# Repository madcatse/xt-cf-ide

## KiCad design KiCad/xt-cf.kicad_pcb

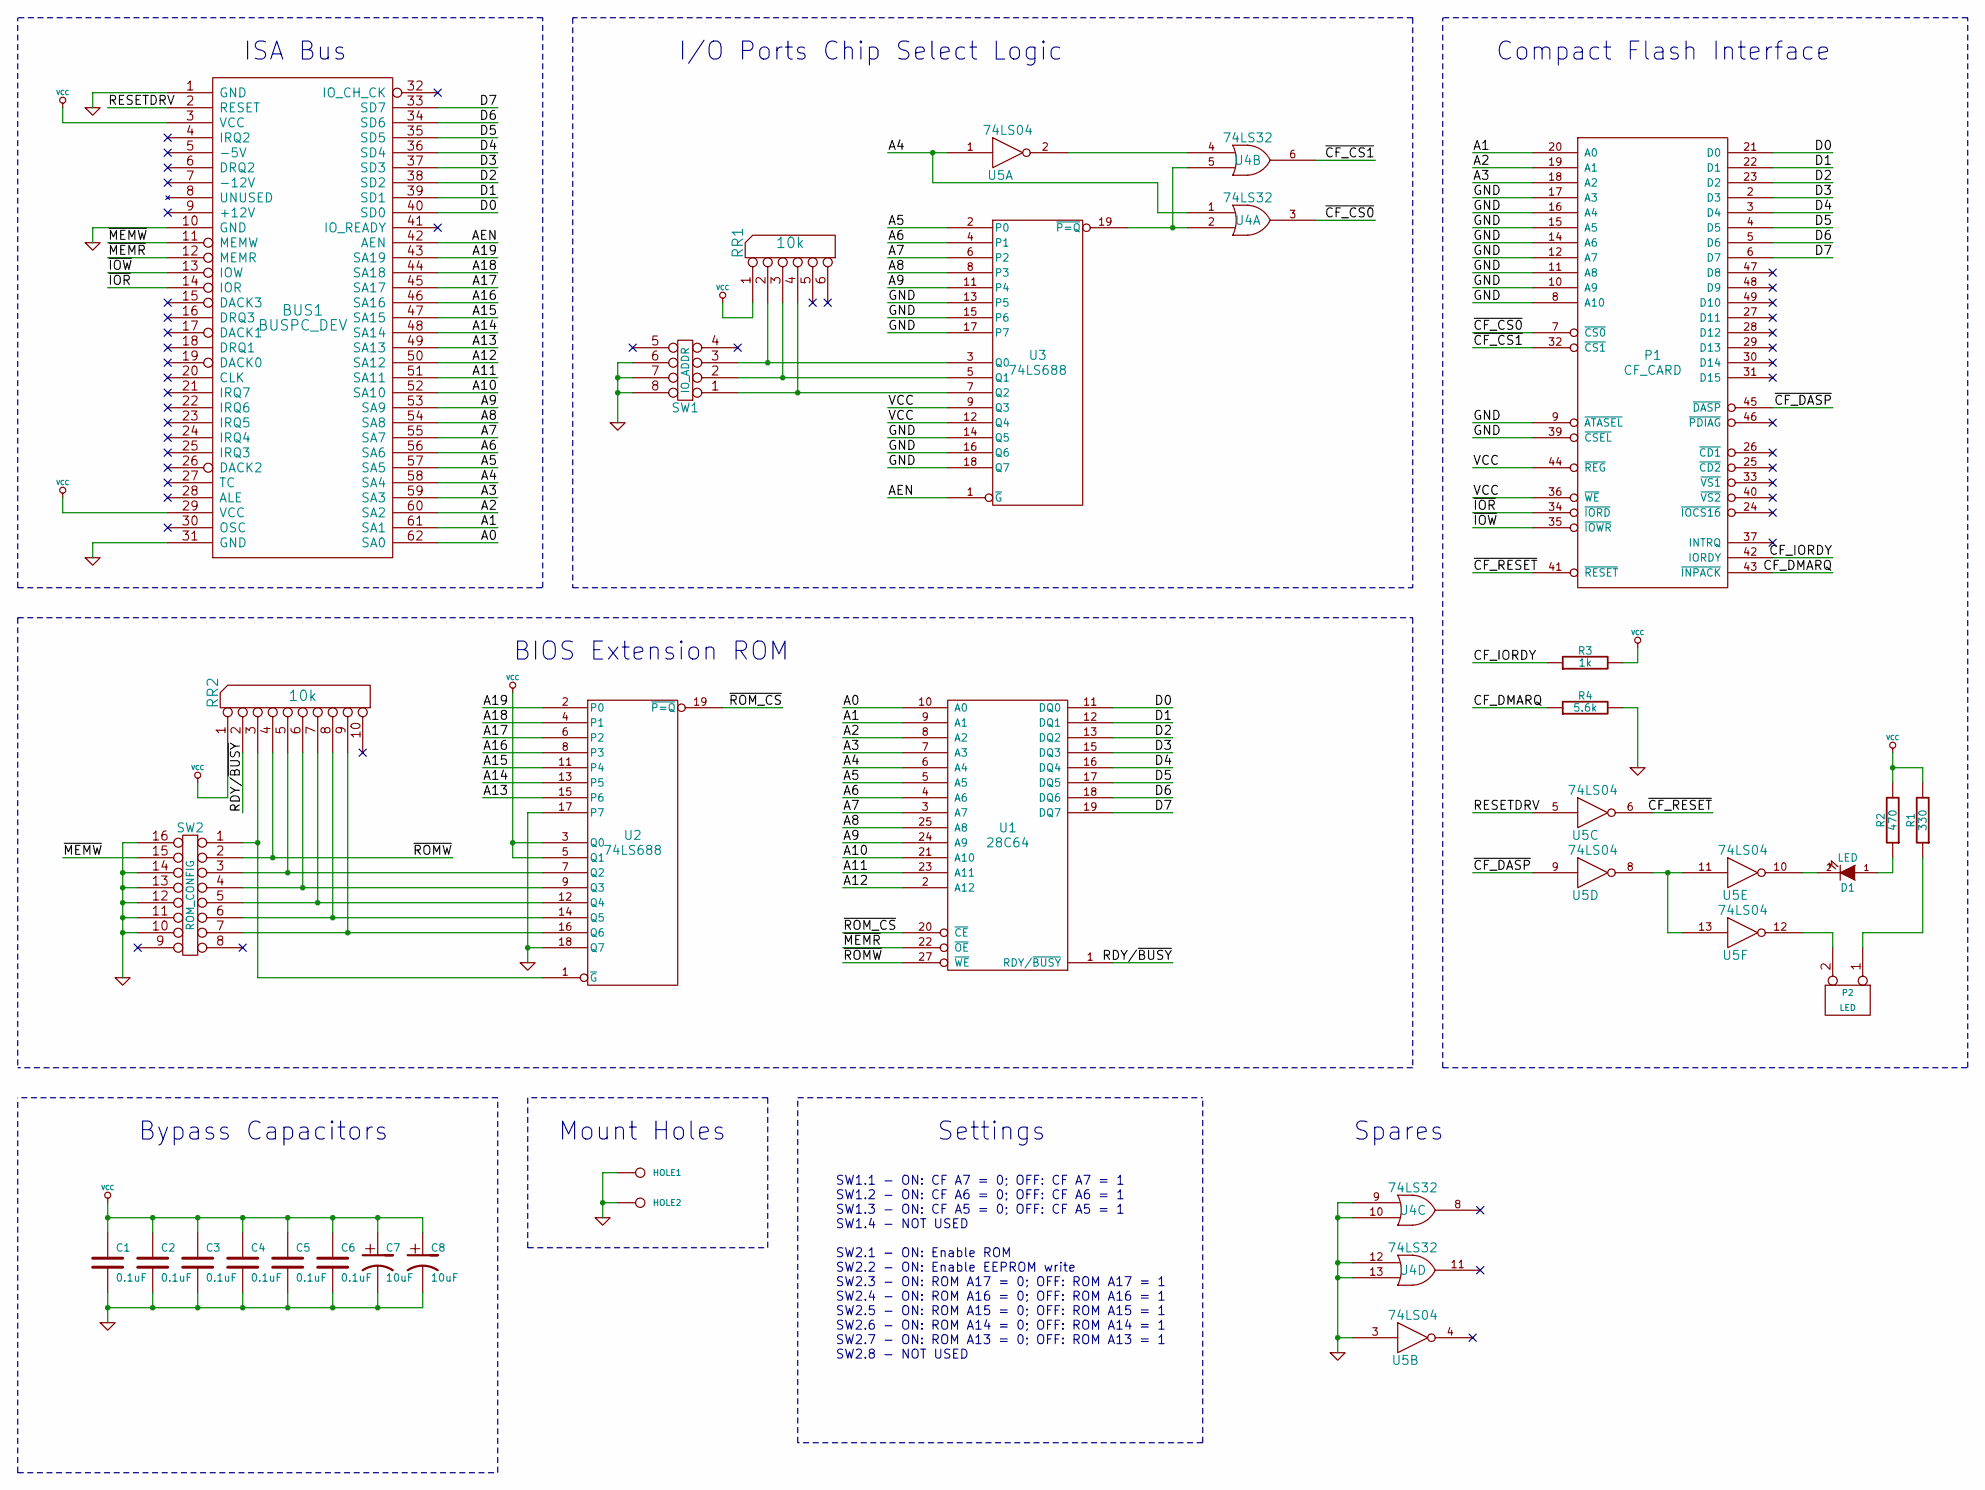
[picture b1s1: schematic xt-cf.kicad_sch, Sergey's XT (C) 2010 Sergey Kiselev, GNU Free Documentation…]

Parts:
BUS1: BUSPC_DEV; Conn_Bus_ISA8
C1, C2, C3, C4, C5, C6: 0.1uF; C_Disc_D7.0mm_W2.5mm_P5.00mm
C7, C8: 10uF; CP_Radial_D8.0mm_P5.00mm
D1: LED; LED_D3.0mm
HOLE1, HOLE2: CONN_1; HOLE_3MM
P1: CF_CARD; CF_N7E50-Q516XX-40
P2: LED; PIN_ARRAY_2X1
R1: 330; R_Axial_DIN0207_L6.3mm_D2.5mm_P7.62mm_Horizontal
R2: 470; R_Axial_DIN0207_L6.3mm_D2.5mm_P7.62mm_Horizontal
R3: 1k; R_Axial_DIN0207_L6.3mm_D2.5mm_P7.62mm_Horizontal
R4: 5.6k; R_Axial_DIN0207_L6.3mm_D2.5mm_P7.62mm_Horizontal
RR1: 10k; SIL-6
RR2: 10k; SIL-10
SW1: IO_ADDR; DIP8_300
SW2: ROM_CONFIG; DIP16_300
U1: 28C64; DIP-28_W15.24mm
U2, U3: 74LS688; DIP-20_W7.62mm
U4: 74LS32; DIP-14_W7.62mm
U5: 74LS04; DIP-14_W7.62mm

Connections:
/A0: BUS1.62 (SA0), U1.10 (A0)
/A1: BUS1.61 (SA1), P1.20 (A0), U1.9 (A1)
/A2: BUS1.60 (SA2), P1.19 (A1), U1.8 (A2)
/A3: BUS1.59 (SA3), P1.18 (A2), U1.7 (A3)
/A4: BUS1.58 (SA4), U1.6 (A4), U4.1, U5.1
/A5: BUS1.57 (SA5), U1.5 (A5), U3.2 (P0)
/A6: BUS1.56 (SA6), U1.4 (A6), U3.4 (P1)
/A7: BUS1.55 (SA7), U1.3 (A7), U3.6 (P2)
/A8: BUS1.54 (SA8), U1.25 (A8), U3.8 (P3)
/A9: BUS1.53 (SA9), U1.24 (A9), U3.11 (P4)
/A10: BUS1.52 (SA10), U1.21 (A10)
/A11: BUS1.51 (SA11), U1.23 (A11)
/A12: BUS1.50 (SA12), U1.2 (A12)
/A13: BUS1.49 (SA13), U2.15 (P6)
/A14: BUS1.48 (SA14), U2.13 (P5)
/A15: BUS1.47 (SA15), U2.11 (P4)
/A16: BUS1.46 (SA16), U2.8 (P3)
/A17: BUS1.45 (SA17), U2.6 (P2)
/A18: BUS1.44 (SA18), U2.4 (P1)
/A19: BUS1.43 (SA19), U2.2 (P0)
/AEN: BUS1.42 (AEN), U3.1 (~G)
/CF_DMARQ: P1.43 (~INPACK), R4.1
/CF_IORDY: P1.42 (IORDY), R3.1
/D0: BUS1.40 (SD0), P1.21 (D0), U1.11 (DQ0)
/D1: BUS1.39 (SD1), P1.22 (D1), U1.12 (DQ1)
/D2: BUS1.38 (SD2), P1.23 (D2), U1.13 (DQ2)
/D3: BUS1.37 (SD3), P1.2 (D3), U1.15 (DQ3)
/D4: BUS1.36 (SD4), P1.3 (D4), U1.16 (DQ4)
/D5: BUS1.35 (SD5), P1.4 (D5), U1.17 (DQ5)
/D6: BUS1.34 (SD6), P1.5 (D6), U1.18 (DQ6)
/D7: BUS1.33 (SD7), P1.6 (D7), U1.19 (DQ7)
/RDY/~BUSY: RR2.2, U1.1 (RDY/~BUSY)
/RESETDRV: BUS1.2 (RESET), U5.5
/~CF_CS0: P1.7 (~CS0), U4.3
/~CF_CS1: P1.32 (~CS1), U4.6
/~CF_DASP: P1.45 (~DASP), U5.9
/~CF_RESET: P1.41 (~RESET), U5.6
/~IOR: BUS1.14 (IOR), P1.34 (~IORD)
/~IOW: BUS1.13 (IOW), P1.35 (~IOWR)
/~MEMR: BUS1.12 (MEMR), U1.22 (~OE)
/~MEMW: BUS1.11 (MEMW), SW2.15
/~ROMW: RR2.4, SW2.2, U1.27 (~WE)
/~ROM_CS: U1.20 (~CE), U2.19 (~P=Q)
GND: BUS1.1 (GND), BUS1.10 (GND), BUS1.31 (GND), C1.2, C2.2, C3.2, C4.2, C5.2, C6.2, C7.2, C8.2, HOLE1.1, HOLE2.1, P1.1 (GND), P1.8 (A10), P1.9 (~ATASEL), P1.10 (A9), P1.11 (A8), P1.12 (A7), P1.14 (A6), P1.15 (A5), P1.16 (A4), P1.17 (A3), P1.39 (~CSEL), P1.50 (GND), R4.2, SW1.6, SW1.7, SW1.8, SW2.10, SW2.11, SW2.12, SW2.13, SW2.14, SW2.16, U1.14 (GND), U2.10 (GND), U2.17 (P7), U2.18 (Q7), U3.10 (GND), U3.13 (P5), U3.14 (Q5), U3.15 (P6), U3.16 (Q6), U3.17 (P7), U3.18 (Q7), U4.7 (GND), U4.9, U4.10, U4.12, U4.13, U5.3, U5.7 (GND)
unnamed: D1.1 (A), R2.1
unnamed: D1.2 (K), U5.10
unnamed: P2.1, R1.1
unnamed: P2.2 (PM), U5.12
unnamed: RR1.4, SW1.1, U3.7 (Q2)
unnamed: RR1.3, SW1.2, U3.5 (Q1)
unnamed: RR1.2, SW1.3, U3.3 (Q0)
unnamed: RR2.5, SW2.3, U2.7 (Q2)
unnamed: RR2.6, SW2.4, U2.9 (Q3)
unnamed: RR2.7, SW2.5, U2.12 (Q4)
unnamed: RR2.8, SW2.6, U2.14 (Q5)
unnamed: RR2.9, SW2.7, U2.16 (Q6)
unnamed: RR2.3, SW2.1, U2.1 (~G)
unnamed: U3.19 (~P=Q), U4.2, U4.5
unnamed: U4.4, U5.2
unnamed: U5.8, U5.11, U5.13
VCC: BUS1.3 (VCC), BUS1.29 (VCC), C1.1, C2.1, C3.1, C4.1, C5.1, C6.1, C7.1, C8.1, P1.13 (VCC), P1.36 (~WE), P1.38 (VCC), P1.44 (~REG), R1.2, R2.2, R3.2, RR1.1 (COM), RR2.1 (COM), U1.28 (VCC), U2.3 (Q0), U2.5 (Q1), U2.20 (VCC), U3.9 (Q3), U3.12 (Q4), U3.20 (VCC), U4.14 (VCC), U5.14 (VCC)

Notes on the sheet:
SW1.1 - ON: CF A7 = 0; OFF: CF A7 = 1 SW1.2 - ON: CF A6 = 0; OFF: CF A6 = 1 SW1.3 - ON: CF A5 = 0; OFF: CF A5 = 1 SW1.4 - NOT USED SW2.1 - ON: Enable ROM SW2.2 - ON: Enable EEPROM write SW2.3 - ON: ROM A17 = 0; OFF: ROM A17 = 1 SW2.4 - ON: ROM A16 = 0; OFF: ROM A16 = 1 SW2.5 - ON: ROM A15 = 0; OFF: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
Bypass Capacitors
ISA Bus
Mount Holes
BIOS Extension ROM
I/O Ports Chip Select Logic
Compact Flash Interface
Spares
Settings

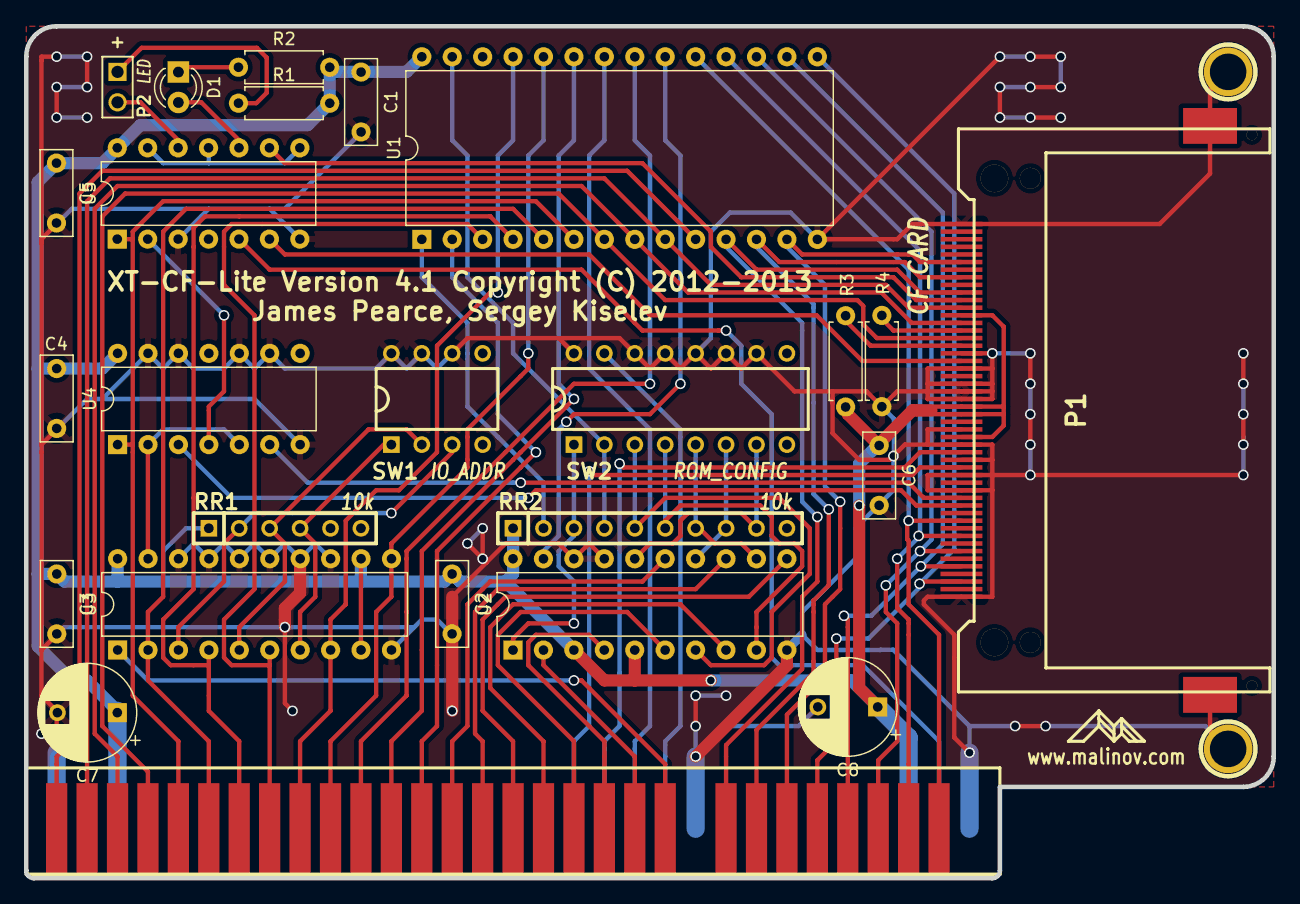
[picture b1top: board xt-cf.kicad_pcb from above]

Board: 2 copper layers, 104.1 x 71.1 mm, 27 parts (0 on the bottom side), 61 nets.

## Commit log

2024-08-11 Prtoject cleanup
    Convert to Kicad7, 10K resistor removed, symbols and footprints moved to local lib, overall cleanup
2024-08-11 BOM generated
2024-12-14 Commit 14122024
2026-04-29 Little fix
2026-05-14 ROMS

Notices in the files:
KiCad/xt-cf.kicad_pcb:
XT-CF-Lite Version 4.1 Copyright (C) 2012-2013
KiCad/xt-cf.kicad_sch:
Sergey's XT (C) 2010 Sergey Kiselev, GNU Free Documentation License (GFDL)
